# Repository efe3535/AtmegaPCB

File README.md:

# My Atmega PCB
This is my first "devboard" pcb. Here, you can download it.
---

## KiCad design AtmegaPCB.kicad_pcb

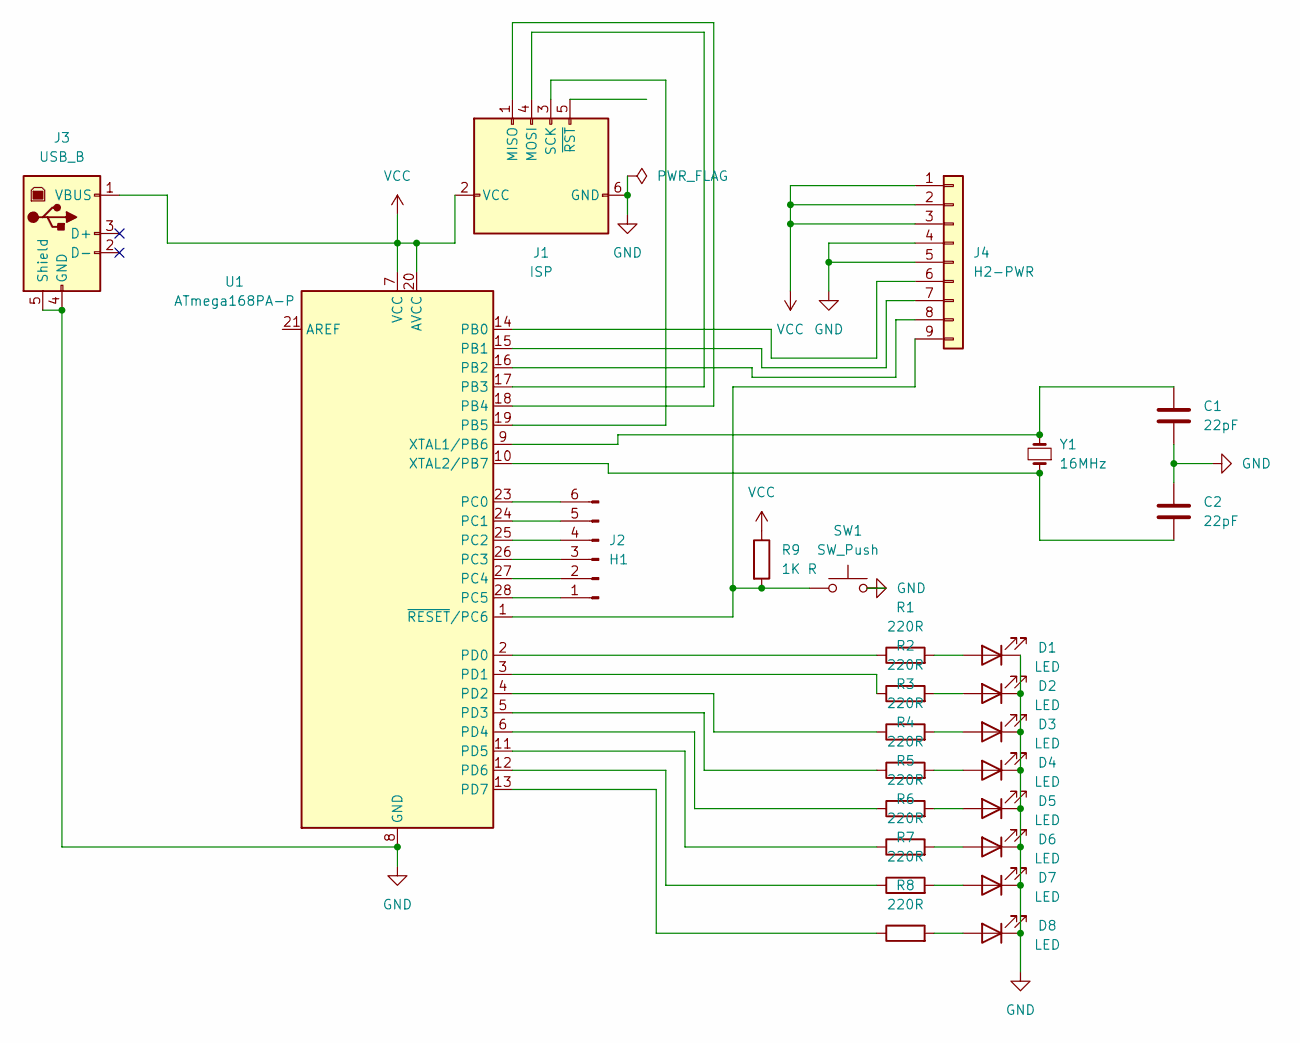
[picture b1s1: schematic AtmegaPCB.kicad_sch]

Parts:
C1, C2: 22pF; C_Axial_L3.8mm_D2.6mm_P7.50mm_Horizontal
D1, D2, D3, D4, D5, D6, D7, D8: LED; LED_D5.0mm_Horizontal_O1.27mm_Z3.0mm
J1: ISP; PinHeader_2x03_P2.54mm_Vertical
J2: H1; PinHeader_1x06_P2.54mm_Vertical
J3: USB_B; USB_B_OST_USB-B1HSxx_Horizontal
J4: H2-PWR; PinHeader_1x09_P2.54mm_Vertical
R1, R2, R3, R4, R5, R6, R7, R8: 220R; R_Axial_DIN0207_L6.3mm_D2.5mm_P7.62mm_Horizontal
R9: 1K R; R_Axial_DIN0207_L6.3mm_D2.5mm_P7.62mm_Horizontal
SW1: SW_Push; SW_PUSH_6mm_H13mm
U1: ATmega168PA-P; zif-28-pin
Y1: 16MHz; Crystal_HC49-4H_Vertical

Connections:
GND: C1.2, C2.1, D1.1 (K), D2.1 (K), D3.1 (K), D4.1 (K), D5.1 (K), D6.1 (K), D7.1 (K), D8.1 (K), J1.6 (GND), J3.4 (GND), J3.5 (Shield), J4.4, J4.5, SW1.2, U1.8 (GND), U1.22 (GND); also elsewhere on the board
unnamed: D1.2 (A), R1.2
unnamed: D2.2 (A), R2.2
unnamed: D3.2 (A), R3.2
unnamed: D4.2 (A), R4.2
unnamed: D5.2 (A), R5.2
unnamed: D6.2 (A), R6.2
unnamed: D7.2 (A), R7.2
unnamed: D8.2 (A), R8.2
unnamed 9: J1.1 (MISO), U1.18 (PB4); also elsewhere on the board
unnamed 10: J1.4 (MOSI), U1.17 (PB3); also elsewhere on the board
unnamed 11: J1.3 (SCK), U1.19 (PB5); also elsewhere on the board
unnamed: J2.1, U1.28 (PC5)
unnamed: J2.2, U1.27 (PC4)
unnamed: J2.3, U1.26 (PC3)
unnamed: J2.4, U1.25 (PC2)
unnamed: J2.5, U1.24 (PC1)
unnamed: J2.6, U1.23 (PC0)
unnamed: J4.6, U1.14 (PB0)
unnamed: J4.7, U1.15 (PB1)
unnamed: J4.8, U1.16 (PB2)
unnamed 21: J4.9, R9.2, SW1.1, U1.1 (~RESET/PC6); also elsewhere on the board
unnamed: R1.1, U1.2 (PD0)
unnamed: R2.1, U1.3 (PD1)
unnamed: R3.1, U1.4 (PD2)
unnamed: R4.1, U1.5 (PD3)
unnamed: R5.1, U1.6 (PD4)
unnamed: R6.1, U1.11 (PD5)
unnamed: R7.1, U1.12 (PD6)
unnamed: R8.1, U1.13 (PD7)
unnamed: C1.1, U1.9 (XTAL1/PB6), Y1.2
unnamed: C2.2, U1.10 (XTAL2/PB7), Y1.1
VCC: J1.2 (VCC), J3.1 (VBUS), J4.1, J4.2, J4.3, R9.1, U1.7 (VCC), U1.20 (AVCC); also elsewhere on the board

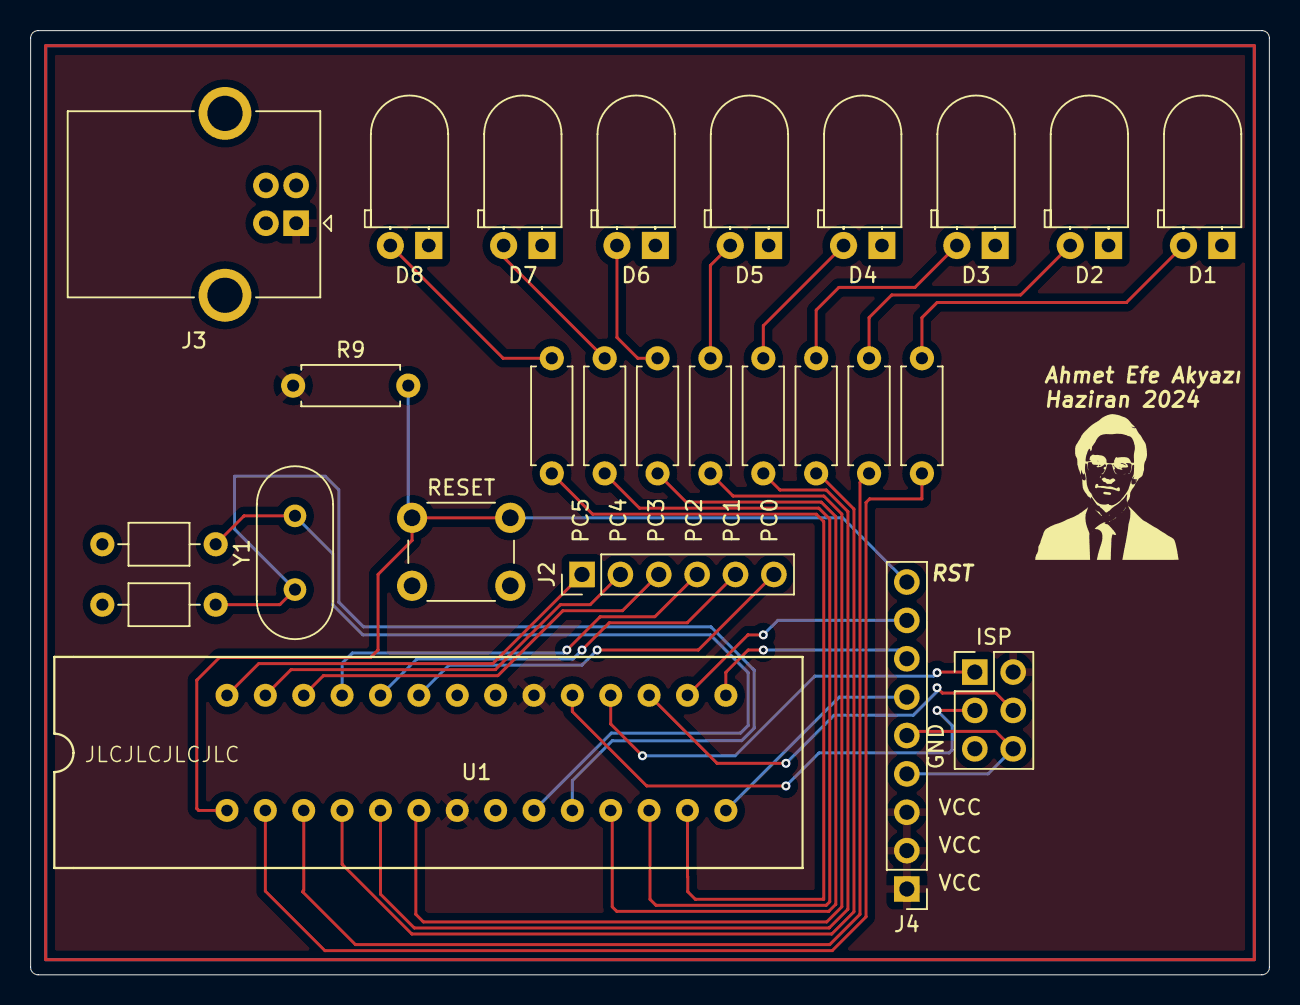
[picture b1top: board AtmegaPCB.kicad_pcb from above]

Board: 2 copper layers, 82.0 x 62.5 mm, 26 parts (0 on the bottom side), 33 nets.

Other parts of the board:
ISP: ISP; PinHeader_2x03_P2.54mm_Vertical
RESET: SW_Push; SW_PUSH_6mm_H13mm

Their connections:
GND: ISP.6 (GND), RESET.2; also elsewhere on the board
unnamed 9: ISP.1 (MISO); also elsewhere on the board
unnamed 10: ISP.4 (MOSI); also elsewhere on the board
unnamed 11: ISP.3 (SCK); also elsewhere on the board
unnamed 21: RESET.1; also elsewhere on the board
VCC: ISP.2 (VCC); also elsewhere on the board

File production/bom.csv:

Designator,Footprint,Quantity,Value,LCSC Part #
"C1, C2",C_Axial_L3.8mm_D2.6mm_P7.50mm_Horizontal,2,22pF,
"D1, D2, D3, D4, D5, D6, D7, D8",LED_D5.0mm_Horizontal_O1.27mm_Z3.0mm,8,LED,
ISP,PinHeader_2x03_P2.54mm_Vertical,1,ISP,
J2,PinHeader_1x06_P2.54mm_Vertical,1,H1,
J3,USB_B_OST_USB-B1HSxx_Horizontal,1,USB_B,
J4,PinHeader_1x09_P2.54mm_Vertical,1,H2-PWR,
"R1, R2, R3, R4, R5, R6, R7, R8",R_Axial_DIN0207_L6.3mm_D2.5mm_P7.62mm_Horizontal,8,220R,
R9,R_Axial_DIN0207_L6.3mm_D2.5mm_P7.62mm_Horizontal,1,1K R,
RESET,SW_PUSH_6mm_H13mm,1,SW_Push,
U1,zif-28-pin,1,ATmega168PA-P,
Y1,Crystal_HC49-4H_Vertical,1,16MHz,

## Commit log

2024-07-06 Add PCB files
2024-07-06 add readme and preview image
